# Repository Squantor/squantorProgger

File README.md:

# SquantProgger JTAG/SWD probe
This repository contains hardware and software for the development of the Squantprogger JTAG/SWD probe.
## What? Another programmer?
Why yes! I was not completely satisfied with the existing solutions. The two leading open source solutions like the [black magic probe](https://github.com/blacksphere/blackmagic/wiki) or the [Cortexprog](https://cortexprog.com/) have a few, in my opinion, flaws that squantProgger tries to overcome. The blackmagic probe requires a new firmware to support new devices, interface clocking is fixed speed, using the GDB interface is not entirely optimal with respect to speedups and error robustness. The Cortexprog uses bitbanged USB HID interface and is SWD only.

I really wanted to combine the strongest features of these two programmers into one package. Device support depends on the PC side software and not the probe, support SWD and JTAG at any reasonable speed (1kHz to 10MHz), be reasonably fast, no or minimal driver installation requirements.
# Repository structure
* hardware: contains the hardware of the various programmer iterations and possible extension boards
* software_embedded: contains the probe software
* software_pc: contains the PC side software
# usage
Check out using ```git clone --recurse-submodules``` as this project uses git submodules for hardware and software components.

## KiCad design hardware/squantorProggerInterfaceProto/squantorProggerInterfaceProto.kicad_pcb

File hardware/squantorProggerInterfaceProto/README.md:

# Prototype for SWD/JTAG logic interface
Prototype level shifting interface for a JTAG/SWD. Operational voltage range is from 5.5V to 1.65V. The TMS switch is handled by a bus switch instead of a dual voltage level shifter. This is to prevent input/output switching on the microcontroller. This way you can more easely chain SPI transactions while using SPI chip enable pins to enable the bus
## TODO's
Still some things need to be done:
* schematic entry (Done)
* PCB layout (Done)
* Review with one night in between (Done)
* Produce at [OSHPARK](https://oshpark.com/shared_projects/nZVJTeq3) (In progress)
* Assemble (TODO)
* Test & characterise (TODO)
# BOM
Use whatever decoupling capacitors you have, most passives are predominantly 0402.
* Most 0402 capacitors for decoupling are 100nF, but 1uF is also suitable
* Series resistor R1, R2 1K can be used, the parallel caps are 22pF. These are to test if any current backflow will occur when the 1G125 is unpowered.
* U1, U2, U3 and U4 are [Diodes Incorporated 74LVC1T45DW-7 from LCSC](https://lcsc.com/product-detail/Interface-ICs_DIODES_74LVC1T45DW-7_74LVC1T45DW-7_C168855.html).
* U5 is a [Nexperia 74LVC1G125GW,125 from LCSC](https://lcsc.com/product-detail/74-Series_NXP_74LVC1G125GW_74LVC1G125GW-125_C12519.html)

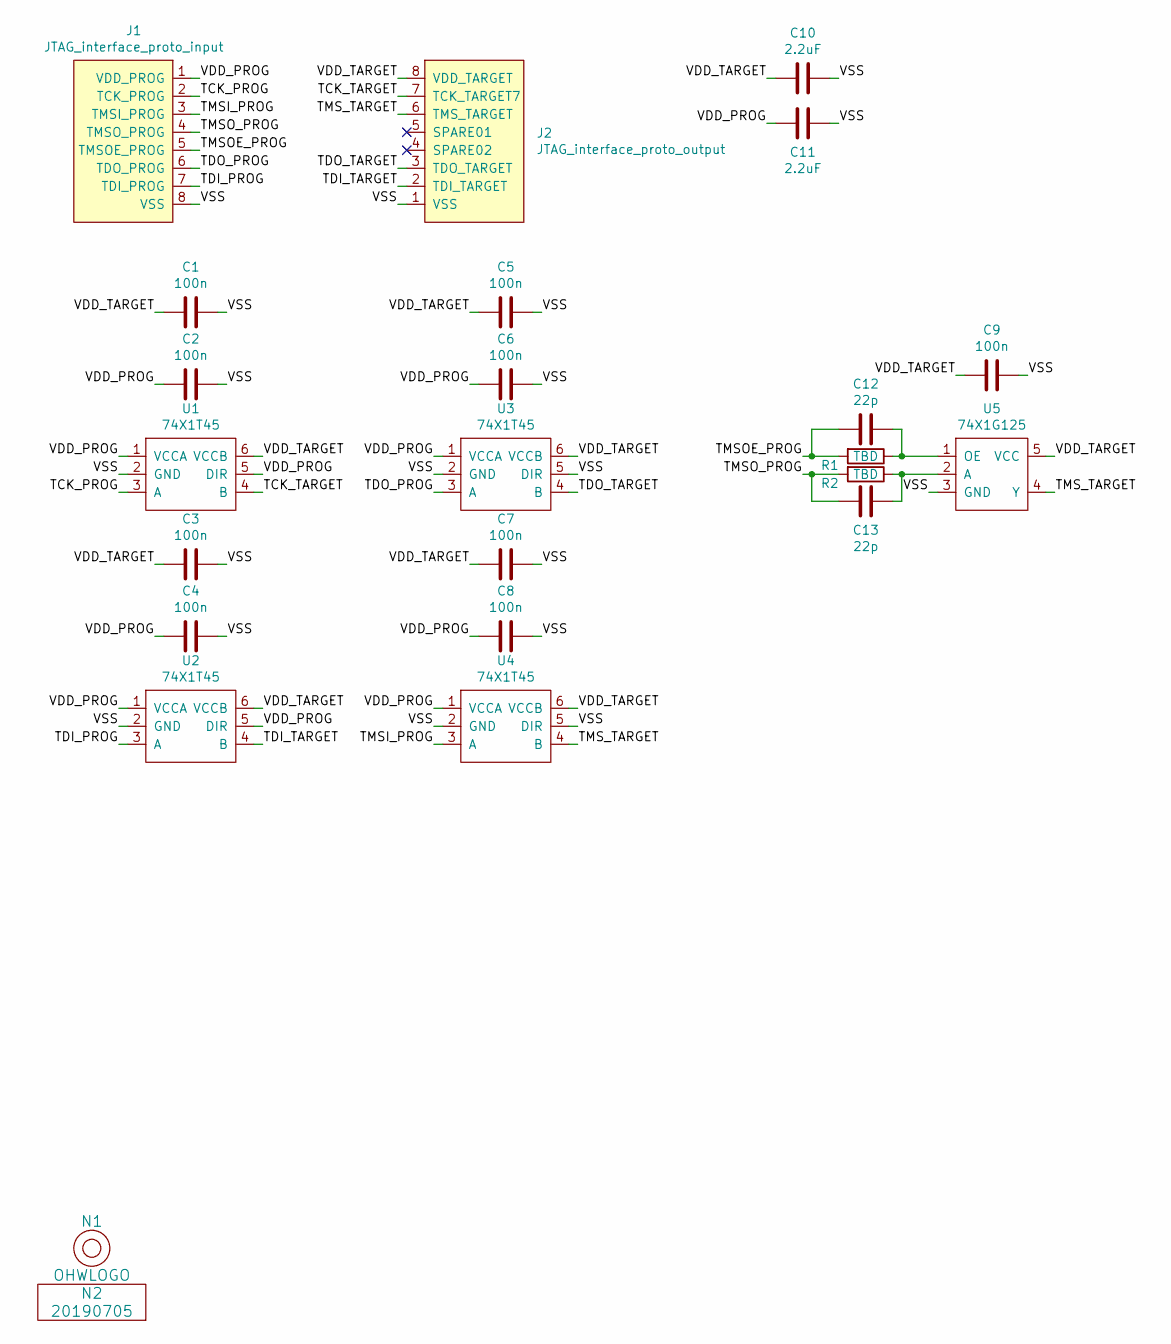
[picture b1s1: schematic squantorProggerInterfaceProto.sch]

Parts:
C1, C2, C3, C4, C5, C6, C7, C8, C9: 100n; C_0402
C10, C11: 2.2uF; C_0805
C12, C13: 22p; C_0402
J1: JTAG_interface_proto_input; JTAG-interface-proto-input
J2: JTAG_interface_proto_output; JTAG-interface-proto-output
N1: OHWLOGO; OSHW-Logo_5.7x6mm_SilkScreen
N2: 20190705; Label_version
R1, R2: TBD; R_0402_hand
U1, U2, U3, U4: 74X1T45; SOT363-hand
U5: 74X1G125; SOT353-hand

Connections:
/TCK_PROG: J1.2 (TCK_PROG), U1.3 (A)
/TCK_TARGET: J2.7 (TCK_TARGET7), U1.4 (B)
/TDI_PROG: J1.7 (TDI_PROG), U2.3 (A)
/TDI_TARGET: J2.2 (TDI_TARGET), U2.4 (B)
/TDO_PROG: J1.6 (TDO_PROG), U3.3 (A)
/TDO_TARGET: J2.3 (TDO_TARGET), U3.4 (B)
/TMSI_PROG: J1.3 (TMSI_PROG), U4.3 (A)
/TMSOE_PROG: C12.2, J1.5 (TMSOE_PROG), R1.2
/TMSO_PROG: C13.2, J1.4 (TMSO_PROG), R2.2
/TMS_TARGET: J2.6 (TMS_TARGET), U4.4 (B), U5.4 (Y)
/VDD_PROG: C2.2, C4.2, C6.2, C8.2, C11.2, J1.1 (VDD_PROG), U1.1 (VCCA), U1.5 (DIR), U2.1 (VCCA), U2.5 (DIR), U3.1 (VCCA), U4.1 (VCCA)
/VDD_TARGET: C1.2, C3.2, C5.2, C7.2, C9.2, C10.2, J2.8 (VDD_TARGET), U1.6 (VCCB), U2.6 (VCCB), U3.6 (VCCB), U4.6 (VCCB), U5.5 (VCC)
/VSS: C1.1, C2.1, C3.1, C4.1, C5.1, C6.1, C7.1, C8.1, C9.1, C10.1, C11.1, J1.8 (VSS), J2.1 (VSS), U1.2 (GND), U2.2 (GND), U3.2 (GND), U3.5 (DIR), U4.2 (GND), U4.5 (DIR), U5.3 (GND)
unnamed: C12.1, R1.1, U5.1 (OE)
unnamed: C13.1, R2.1, U5.2 (A)

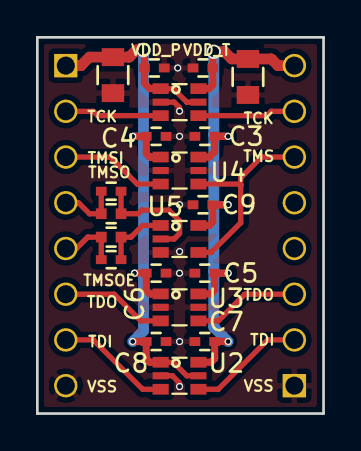
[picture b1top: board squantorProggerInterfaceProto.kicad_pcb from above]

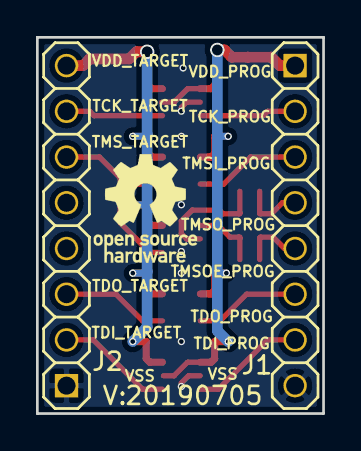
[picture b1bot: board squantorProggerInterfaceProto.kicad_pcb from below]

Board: 2 copper layers, 15.9 x 20.9 mm, 24 parts (4 on the bottom side), 15 nets.

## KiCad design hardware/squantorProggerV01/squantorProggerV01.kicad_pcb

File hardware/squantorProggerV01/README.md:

# SquantorProgger JTAG/SWD probe version 0.1
This is the initial hardware creation of the SquantorProgger hardware to do some design exploration and figure out how to build a JTAG/SWD probe from scratch.
## Hardware architecture
The SquantProgger talks to the host system via the [CH340E](http://wch.cn/downloads/CH340DS1_PDF.html) USB to serial converter to the microcontroller [LPC824](https://www.nxp.com/products/processors-and-microcontrollers/arm-based-processors-and-mcus/lpc-cortex-m-mcus/lpc800-series-cortex-m0-plus-mcus/low-cost-microcontrollers-mcus-based-on-arm-cortex-m0-plus-cores:LPC82X), communication occurs at a baud rate of 1Mbaud. The CH340E also provides a reset signal via the flow control pins to reset the LPC824 and access the bootloader. The LPC824 contains the software to translate protocol calls into JTAG/SWD communication. A single output driver (74X1G125 logic chip) provides disabling of the TMS driver. The voltage level of the signals is fixed at 3.3V. The power is provided by a MCP1702 LDO. A dual P channel mosfet facilitates power switching to the target.
## HSI (Hardware Software Interface)
Description of the various connections on software programmable components.
### LPC824
### CH340E
## TODO's
Still some things need to be done:
* filling initial functions in the HSI (TODO)
* schematic entry (TODO)
* PCB layout (TODO)
* Review with one night in between (TODO)
* Produce at [OSHPARK](https://oshpark.com/) (TODO)
* Assemble (TODO)
* Test & characterise (TODO)
* update Readme.md with pictures and BOM (TODO)

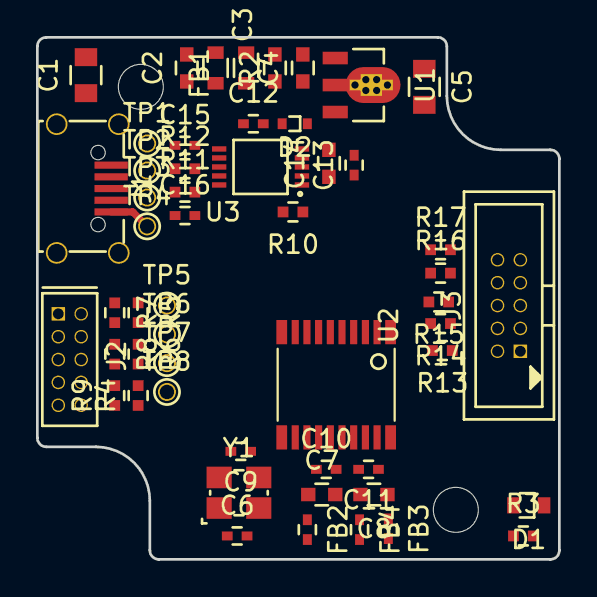
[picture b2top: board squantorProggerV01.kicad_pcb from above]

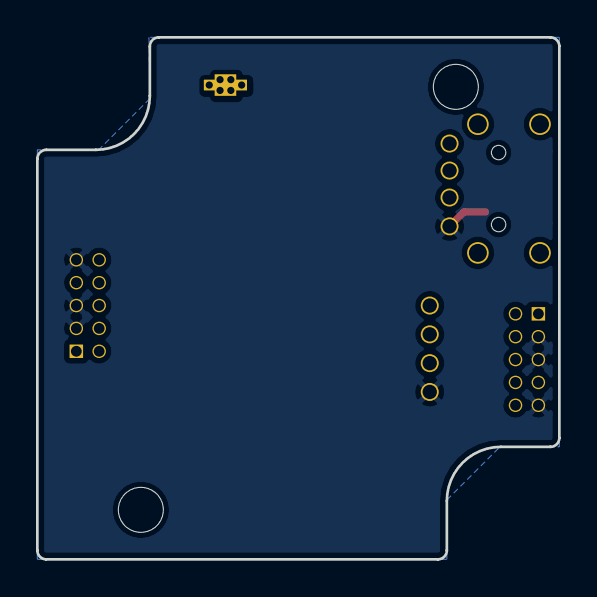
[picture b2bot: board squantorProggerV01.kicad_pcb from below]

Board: 2 copper layers, 29.0 x 29.0 mm, 57 parts (2 on the bottom side), 29 nets.

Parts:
C1: 100n; C_0805
C2: 100n; C_0603
C3, C4, C7, C8, C14: 1u; C_0603
C5: 10u; C_0805
C6, C9: 18p; C_0402
C10, C11, C12, C13: 100n; C_0402
C15, C16: 47p; C_0402
D1: RED; D_0603_hand
D2: D; SOD-523
FB1: 600; R_0603_hand
FB2, FB3, FB4: FB; C_0402
H1, H2: Drill_Hole_no_metal; MountingHole_2.5mm_no_metal
J1: USB-ID; USB-muB-SMD_TH
J2: JTAG_2X05; Header-0127-2X05-H006
J3: JTAG_2X05_OUT; Header-Shr-0127-2X05-H006
N1: OHWLOGO; OSHW-Symbol_6.7x6mm_SilkScreen
N2: 20190520; Label_version
R2: Fuse; R_0603_hand
R3: 1K; R_0402_hand
R4: 100K; R_0402_hand
R5, R6: 100k; R_0402_hand
R7, R8, R9, R13, R14, R15, R16, R17: 100; R_0402_hand
R10: 10K; R_0402_hand
R11, R12: 33; R_0402_hand
TP1, TP2, TP3, TP4, TP5, TP6, TP7, TP8: testpad; TestPoint_Hole_D0.8mm
U1: MCP1702-MB; SOT89-ViaTab-Microchip-MB
U2: LPC824M201JDH20; SOT360
U3: HT42B534-MSOP10; MSOP-10
Y1: 12MHz; Crystal_3225_4

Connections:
/HT42B534 application example/V33O: C14.1, U3.2
/PIO0_2: R5.2, R7.2, TP5.1, U2.8
/PIO0_3: R6.2, R8.2, TP6.1, U2.7
/PIO0_8: C9.1, U2.14, Y1.3
/PIO0_9: C6.1, U2.13, Y1.1
/RESET: R4.2, R9.2, TP7.1, U2.5
/TXO: R10.1, U3.5
/USB_D+: J1.3, R11.1, TP3.1
/USB_D-: J1.2, R12.1, TP2.1
/VBUS: C2.1, J1.1, R2.2, TP1.1
/VBUS_FILT: C3.1, C13.1, D2.1, FB1.1, U1.2, U1.TAB, U3.1
/VDD: C4.1, C5.2, C12.1, D2.2, FB2.2, FB3.2, J2.1, R3.2, R4.1, R5.1, R10.2, U1.3, U3.6
unnamed: C1.1, J1.S
unnamed: C7.1, C10.1, FB2.1, U2.15
unnamed: C8.1, C11.1, FB3.1, U2.18
unnamed: C8.2, C11.2, FB4.1, U2.17
unnamed: C15.2, R12.2, U3.9
unnamed: C16.2, R11.2, U3.10
unnamed: D1.2, R3.1
unnamed: FB1.2, R2.1
unnamed: J2.2, R7.1
unnamed: J2.4, R8.1
unnamed: J2.10, R9.1
unnamed: J3.2, R13.1
unnamed: J3.4, R14.1
unnamed: J3.6, R15.1
unnamed: J3.8, R16.1
unnamed: J3.10, R17.1
VSS: C1.2, C2.2, C3.2, C4.2, C5.1, C6.2, C7.2, C9.2, C10.2, C12.2, C13.2, C14.2, C15.1, C16.1, D1.1, FB4.2, J1.5, J2.3, J2.5, J2.9, J3.3, J3.5, J3.9, R6.1, TP4.1, TP8.1, U1.1, U2.16, U3.3, Y1.2, Y1.4

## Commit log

2019-03-08 further updates to readme
2019-03-08 initial population of submodules
2019-03-08 added readme for hardware
2019-03-08 removed old submodule position
2019-03-08 added lpcchip library for LPC824
2019-03-08 added squantorProggerV01 hardware project based on kicad template for the Hammond 1551M project box, 2 layer OSHpark
2019-03-08 added gitignore
2019-03-08 placed connectors
2019-03-08 ignoring more kicad intermediates
2019-03-08 updated squantorprogger V0.1 hardware description
2019-03-08 small update
2019-03-09 newer Pcb library, started usb serial bits
2019-04-02 newer kicad libraries
2019-04-02 cleanup of obsolete parts
2019-04-02 imported schematics of LPC824 breakout and HT42B534 breakout
2019-04-06 added HT42B534 application schematic
2019-04-06 added info cache
2019-04-06 added test points to USB and SWD in
2019-05-20 updated component library
2019-05-20 updated footprint
2019-07-02 newer pcb library
2019-07-02 added prototype JTAG/SWD interface
2019-07-02 added fp-info-cache to ignores
2019-07-02 added named connectors from library
2019-07-02 completed schematic, passes DRC
2019-07-03 added newer library adding SOT353 footprints
2019-07-03 added rail decoupling
2019-07-03 footprints defined for level shifter IC's
2019-07-03 initial placement of components
2019-07-04 added named connectors to schematic, moved silk
2019-07-04 routing completed, no DRC errors
2019-07-04 front silk nicely placed
2019-07-04 bottom silk placed
2019-07-04 changed OSH logo, front silk mistake fixed
2019-07-05 final checks, in production
2019-07-05 updated Readme for JTAG interface prototype board
2019-07-05 added libc and libembeddedC
2019-07-05 copied over LPC824 template
2019-07-05 ignoring build intermediates
2019-07-05 updated codelite project files
2019-07-05 added newer lpc chip variant
2019-07-05 copied over basic uart init
2019-07-05 UART output functional
2019-07-05 command interpreter works
2019-07-05 updated Readme with more expanded documentation
2019-07-05 added initial SPI initialization
2019-07-05 initial start on SPI driver
2019-07-05 added TODOs for SPI driver
2019-07-20 updated linker files
2019-07-20 updated libc
2019-07-20 updated build system
2019-07-21 newer libc and libembedded
2019-07-21 updated to newer command mini API
2019-07-21 added required argument to libembeddedc
2019-07-21 fixed compilation problem
2019-07-21 newer libembeddedc
2019-07-21 added systick stuff
2019-07-21 updated libembedded
2019-07-22 removing alive message printing
2019-07-22 WIP: adding spi test command to prompt
2019-07-24 updated lib embedded
2019-07-24 renamed newline string
2019-07-24 newer embedded C library
2019-07-24 completed spi test command parsing
2019-07-27 added SWD pins initialisation
2019-07-27 added SWD pins control to board HAL
2019-07-27 added pin and gpio definitions and properly initialized them
2019-07-27 added swdenable and swddisable commands
2019-07-27 fixed pin definitions, they where wrong!
2019-07-27 finally got some SPI output
2019-07-27 added divisor argument to swd enable
2019-07-27 WIP slave select pins
2019-07-28 fixed incorrect slave select
